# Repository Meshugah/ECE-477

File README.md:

# ECE 477 website backup

Senior design project website details.

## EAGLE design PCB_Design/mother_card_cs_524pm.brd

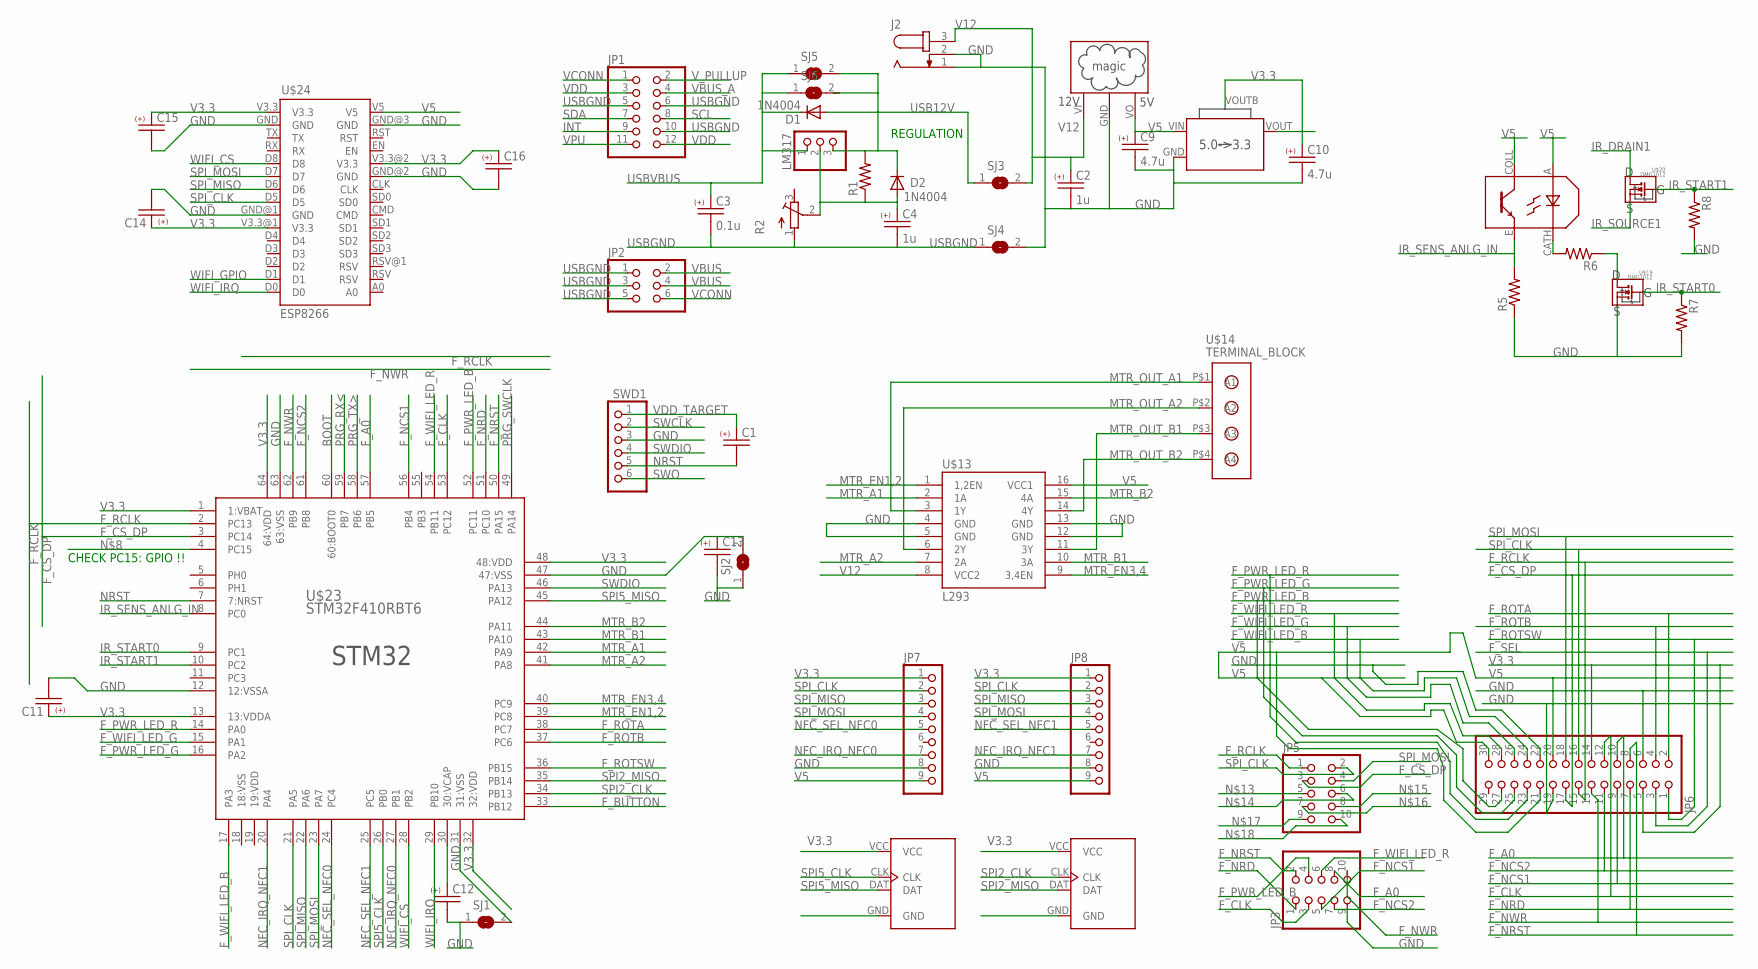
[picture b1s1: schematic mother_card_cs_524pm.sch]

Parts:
C1, C11, C12, C13, C14, C15, C16: C-USC0805; C0805
C2, C4: 1u; C0805
C3: 0.1u; C0805
C9, C10: 4.7u; C0805
D1, D2: 1N4004; DO41-10
J2: JACK-PLUG0; SPC4077
JP1: PINHD-2X6; 2X06
JP2: PINHD-2X3; 2X03
JP3, JP5: PINHD-2X5; 2X05
JP6: PINHD-2X15/SOCK; 2X15/SOCK
JP7, JP8: PINHD-1X9/90; 1X09/90
LM317: PINHD-1X3; 1X03
R1, R5, R6, R7, R8: R-US_R0805; R0805
R2: R-TRIMM64W; RTRIM64W
SJ1, SJ2, SJ3, SJ4, SJ5, SJ6: SJ
SWD1: PINHD-1X6; 1X06
U$13: L293; DIL16
U$14: TERMINAL_BLOCK; 1X4/BLOCK
U$15: AP2114H
U$16: OKI-78SR-W36; SIP3
U$18: TCRT5000
U$19, U$20: DMG1012; SOT323
U$21, U$22: HX711
U$23: STM32F410RBT6; QFP50P1200X1200X160-64N
U$24: ESP8266

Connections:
BOOT: U$23.60 (60:BOOT0)
F_A0: JP3.8, JP6.10, U$23.57 (PB5)
F_BUTTON: U$23.33 (PB12)
F_CLK: JP3.3, JP6.12, U$23.53 (PC12)
F_CS_DP: JP5.3, JP6.17, U$23.3 (PC14)
F_NCS1: JP3.5, JP6.9, U$23.56 (PB4)
F_NCS2: JP3.7, JP6.11, U$23.61 (PB8)
F_NRD: JP3.1, JP6.7, U$23.51 (PC10)
F_NRST: JP3.2, JP6.8, U$23.50 (PA15)
F_NWR: JP3.10, JP6.13, U$23.62 (PB9)
F_PWR_LED_B: JP3.4, JP6.27, U$23.52 (PC11)
F_PWR_LED_G: JP6.25, U$23.16 (PA2)
F_PWR_LED_R: JP6.23, U$23.14 (PA0)
F_RCLK: JP5.1, JP6.15, U$23.2 (PC13)
F_ROTA: JP6.2, U$23.38 (PC7)
F_ROTB: JP6.4, U$23.37 (PC6)
F_ROTSW: JP6.1, U$23.36 (PB15)
F_SEL: JP6.3
F_WIFI_LED_B: JP6.24, U$23.17 (PA3)
F_WIFI_LED_G: JP6.26, U$23.15 (PA1)
F_WIFI_LED_R: JP3.6, JP6.28, U$23.54 (PB11)
GND: C2.2, C9.2, C10.2, C11.2, C12.2, C13.1, C14.2, C15.2, C16.2, J2.1, J2.2, JP3.9, JP6.6, JP6.19, JP6.22, JP7.8, JP8.8, R5.1, R7.2, R8.2, SJ1.1, SJ1.2, SJ2.2, SJ4.2, SWD1.3, U$13.4 (GND), U$13.5 (GND), U$13.12 (GND), U$13.13 (GND), U$15.GND, U$16.GND, U$19.S, U$21.GND, U$22.GND, U$23.12 (12:VSSA), U$23.31 (31:VSS), U$23.47 (47:VSS), U$23.63 (63:VSS), U$24.GND, U$24.GND@1 (GND), U$24.GND@2 (GND), U$24.GND@3 (GND)
INT: JP1.9
IR_DRAIN1: U$20.D
IR_SENS_ANLG_IN: R5.2, U$18.E, U$23.8 (PC0)
IR_SOURCE1: U$20.S
IR_START0: R7.1, U$19.G, U$23.9 (PC1)
IR_START1: R8.1, U$20.G, U$23.10 (PC2)
MTR_A1: U$13.2 (1A), U$23.42 (PA9)
MTR_A2: U$13.7 (2A), U$23.41 (PA8)
MTR_B1: U$13.10 (3A), U$23.43 (PA10)
MTR_B2: U$13.15 (4A), U$23.44 (PA11)
MTR_EN1,2: U$13.1 (1,2EN), U$23.39 (PC8)
MTR_EN3,4: U$13.9 (3,4EN), U$23.40 (PC9)
MTR_OUT_A1: U$13.3 (1Y), U$14.P$1 (A1)
MTR_OUT_A2: U$13.6 (2Y), U$14.P$2 (A2)
MTR_OUT_B1: U$13.11 (3Y), U$14.P$3 (A3)
MTR_OUT_B2: U$13.14 (4Y), U$14.P$4 (A4)
unnamed: C12.1, U$23.30 (30:VCAP)
unnamed: C13.2, SJ2.1
unnamed: C4.1, D2.A, LM317.2, R1.1, R2.2 (S)
unnamed: R6.2, U$18.CATH
unnamed: R6.1, U$19.D
NFC_IRQ_NFC0: JP7.7, U$23.27 (PB1)
NFC_IRQ_NFC1: JP8.7, U$23.20 (PA4)
NFC_SEL_NFC0: JP7.5, U$23.24 (PC4)
NFC_SEL_NFC1: JP8.5, U$23.25 (PC5)
NRST: C1.2, SWD1.5, U$23.7 (7:NRST)
PRG_RX<: U$23.59 (PB7)
PRG_SWCLK: U$23.49 (PA14)
PRG_TX>: U$23.58 (PB6)
SCL: JP1.8
SDA: JP1.7
SPI2_CLK: U$22.CLK, U$23.34 (PB13)
SPI2_MISO: U$22.DAT, U$23.35 (PB14)
SPI5_CLK: U$21.CLK, U$23.26 (PB0)
SPI5_MISO: U$21.DAT, U$23.45 (PA12)
SPI_CLK: JP5.2, JP6.16, JP7.2, JP8.2, U$23.21 (PA5), U$24.D5
SPI_MISO: JP7.3, JP8.3, U$23.22 (PA6), U$24.D6
SPI_MOSI: JP5.4, JP6.18, JP7.4, JP8.4, U$23.23 (PA7), U$24.D7
SWCLK: SWD1.2
SWDIO: SWD1.4, U$23.46 (PA13)
SWO: SWD1.6
USB12V: D1.A, D2.C, LM317.3, R1.2, SJ3.1, SJ5.2
USBGND: C3.2, C4.2, JP1.5, JP1.6, JP1.10, JP2.1, JP2.3, JP2.5, R2.1 (A), SJ4.1
USBVBUS: C3.1, D1.C, LM317.1, SJ5.1, SJ6.1
V3.3: C10.1, C11.1, C14.1, C15.1, C16.1, JP6.5, JP6.14, JP7.1, JP8.1, U$15.VOUT (VO), U$15.VOUTB (BODY), U$21.VCC, U$22.VCC, U$23.1 (1:VBAT), U$23.13 (13:VDDA), U$23.32 (32:VDD), U$23.48 (48:VDD), U$23.64 (64:VDD), U$24.V3.3, U$24.V3.3@1 (V3.3), U$24.V3.3@2 (V3.3)
V5: C9.1, JP6.20, JP6.21, JP6.30, JP7.9, JP8.9, U$13.16 (VCC1), U$15.VIN (VI), U$16.VO, U$18.A, U$18.COLL, U$24.V5
V12: C2.1, J2.3, SJ3.2, U$13.8 (VCC2), U$16.VI
VBUS: JP2.2, JP2.4
VBUS_A: JP1.4
VCONN: JP1.1, JP2.6
VDD: JP1.3, JP1.12
VDD_TARGET: C1.1, SWD1.1
VPU: JP1.11
V_PULLUP: JP1.2
WIFI_CS: U$23.28 (PB2), U$24.D8
WIFI_GPIO: U$24.D1
WIFI_IRQ: U$23.29 (PB10), U$24.D0

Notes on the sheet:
REGULATION
CHECK PC15: GPIO !!

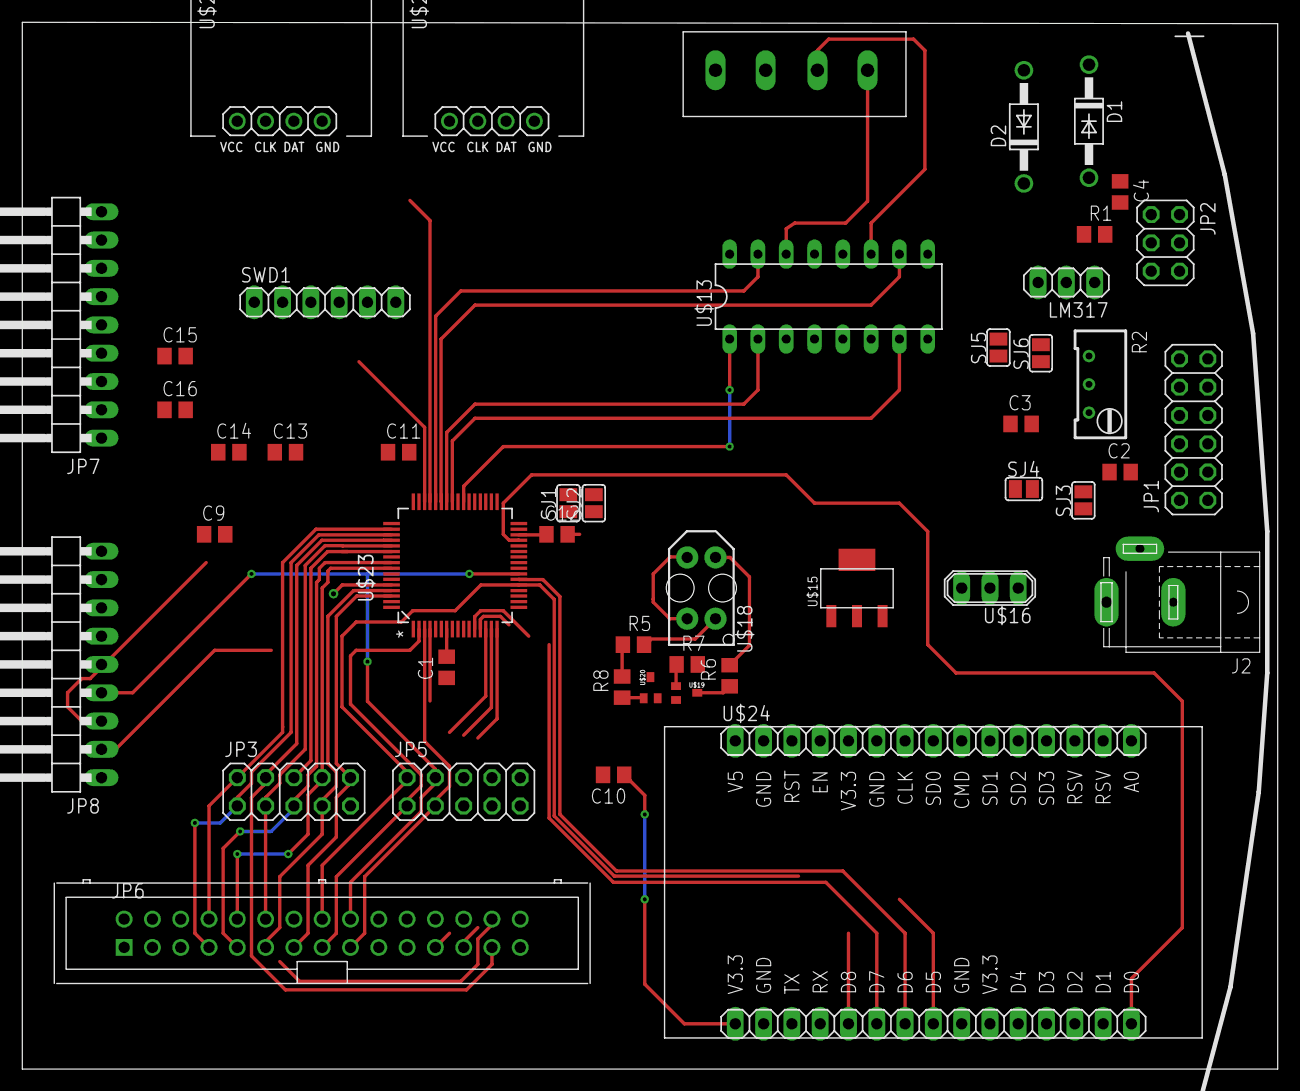
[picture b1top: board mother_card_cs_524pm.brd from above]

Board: 2 copper layers, 112.7 x 94.0 mm, 47 parts (0 on the bottom side), 62 nets.

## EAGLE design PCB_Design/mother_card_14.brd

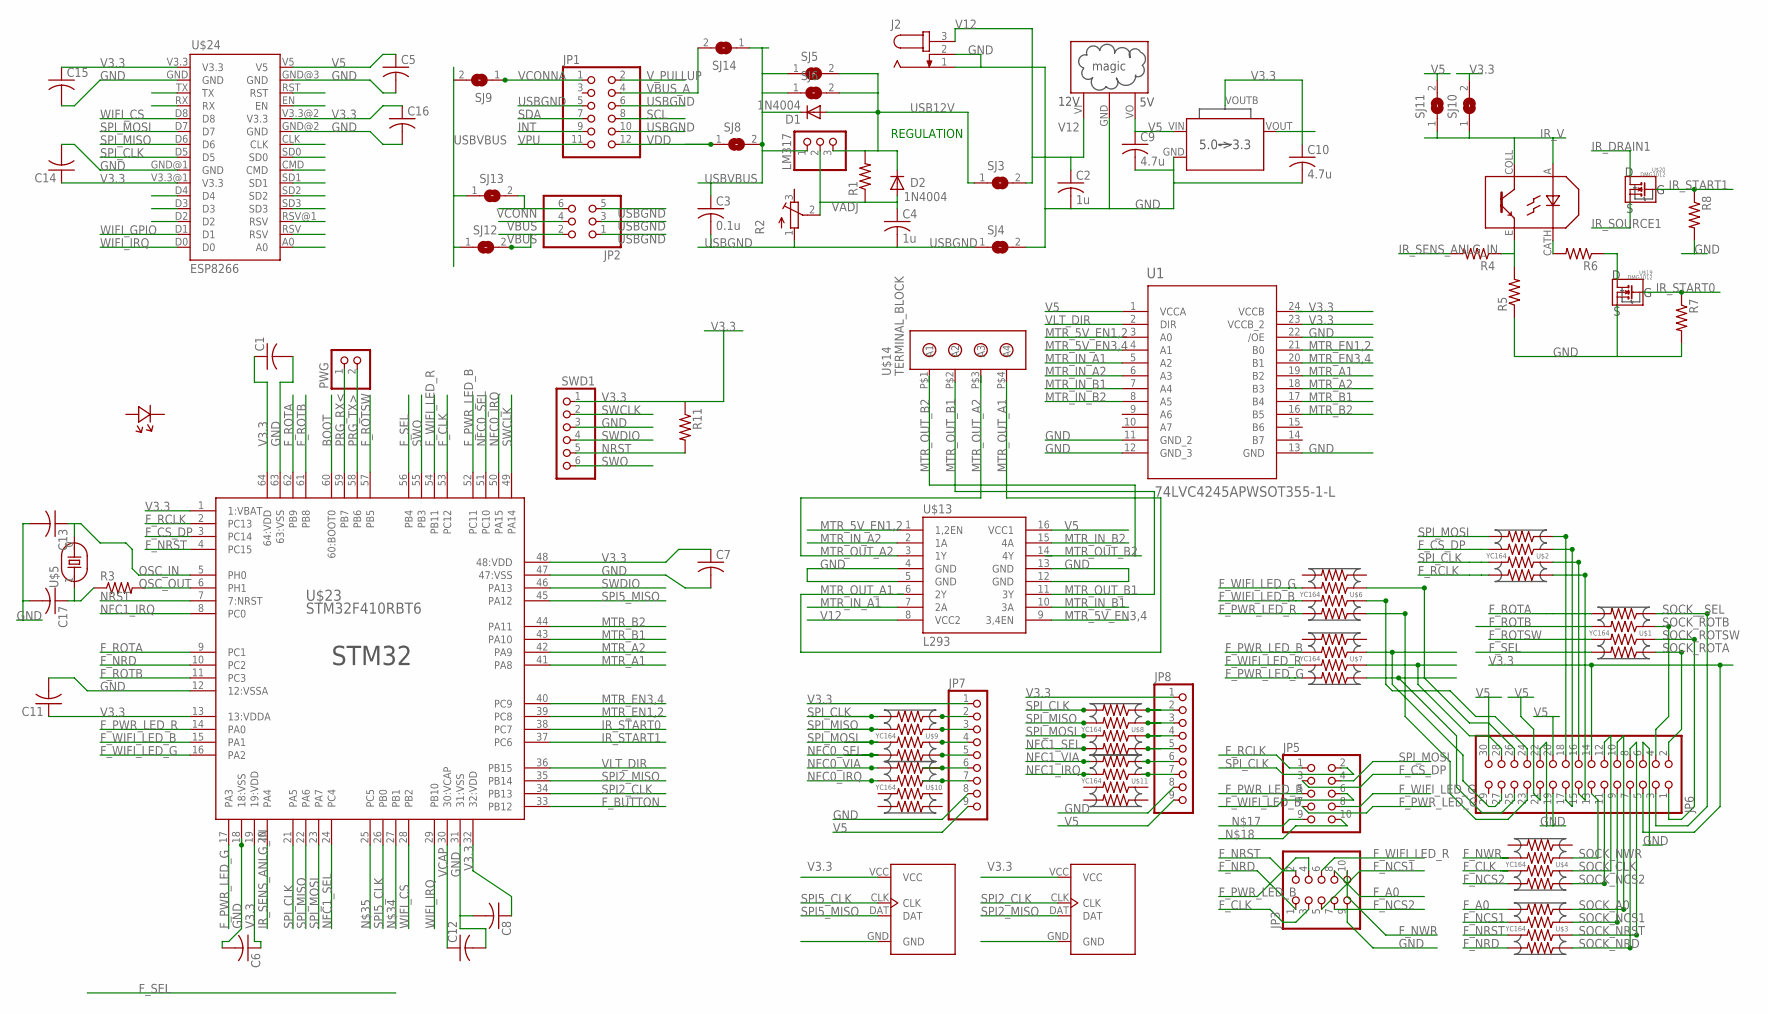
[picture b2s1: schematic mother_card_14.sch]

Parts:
C1, C5, C6, C7, C8, C11, C12, C14, C15, C16: C-USC0805; C0805
C2, C4: 1u; C0805
C3: 0.1u; C0805
C9, C10: 4.7u; C0805
C13, C17: C-USC0603; C0603
D1, D2: 1N4004; DO41-10
J2: JACK-PLUG0; SPC4077
JP1: PINHD-2X6; 2X06
JP2: PINHD-2X3; 2X03
JP3, JP5: PINHD-2X5; 2X05
JP6: PINHD-2X15/SOCK; 2X15/SOCK
JP7, JP8: PINHD-1X9/90; 1X09/90
LM317: PINHD-1X3; 1X03
PWG: PINHD-1X2; 1X02
R1, R3, R4, R5, R6, R7, R8, R11: R-US_R0805; R0805
R2: R-TRIMM64W; RTRIM64W
SJ3, SJ4, SJ5, SJ6, SJ8, SJ9, SJ10, SJ11, SJ12, SJ13, SJ14: SJ
SWD1: PINHD-1X6; 1X06
U1: 74LVC4245APWSOT355-1-L; SOT355-1-L
U$1, U$2, U$3, U$4, U$6, U$7, U$8, U$9, U$10, U$11: YC164
U$5: HC-49S_9B
U$12: LED0603; LED
U$13: L293; DIL16
U$14: TERMINAL_BLOCK; 1X4/BLOCK
U$15: AP2114H
U$16: OKI-78SR-W36; SIP3
U$18: TCRT5000
U$19, U$20: DMG1012; SOT323
U$21, U$22: HX711
U$23: STM32F410RBT6; QFP50P1200X1200X160-64N
U$24: ESP8266

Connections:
BOOT: U$23.60 (60:BOOT0)
F_A0: JP3.8, U$3.P$4 (4)
F_BUTTON: U$23.33 (PB12)
F_CLK: JP3.3, U$4.P$2 (2), U$23.53 (PC12)
F_CS_DP: JP5.3, U$2.P$3 (3), U$23.3 (PC14)
F_NCS1: JP3.5, U$3.P$3 (3)
F_NCS2: JP3.7, U$4.P$1 (1)
F_NRD: JP3.1, U$3.P$1 (1), U$23.10 (PC2)
F_NRST: JP3.2, U$3.P$2 (2), U$23.4 (PC15)
F_NWR: JP3.10, U$4.P$3 (3)
F_PWR_LED_B: JP3.4, U$7.P$3 (3), U$23.52 (PC11)
F_PWR_LED_G: JP5.7, U$7.P$1 (1), U$23.17 (PA3)
F_PWR_LED_R: JP5.5, U$6.P$1 (1), U$23.14 (PA0)
F_RCLK: JP5.1, U$2.P$1 (1), U$23.2 (PC13)
F_ROTA: U$1.P$4 (4), U$23.9 (PC1), U$23.62 (PB9)
F_ROTB: U$1.P$3 (3), U$23.11 (PC3), U$23.61 (PB8)
F_ROTSW: U$1.P$2 (2), U$23.57 (PB5)
F_SEL: U$1.P$1 (1), U$23.56 (PB4)
F_WIFI_LED_B: JP5.6, U$6.P$2 (2), U$23.15 (PA1)
F_WIFI_LED_G: JP5.8, U$6.P$3 (3), U$23.16 (PA2)
F_WIFI_LED_R: JP3.6, U$7.P$2 (2), U$23.54 (PB11)
GND: C1.2, C2.2, C5.2, C6.2, C7.2, C8.2, C9.2, C10.2, C11.2, C12.2, C13.2, C14.2, C15.2, C16.2, C17.2, J2.1, J2.2, JP3.9, JP6.6, JP6.19, JP6.22, JP7.8, JP8.8, R5.1, R7.2, R8.2, SJ4.2, SWD1.3, U1.11 (GND_2), U1.12 (GND_3), U1.13 (GND), U1.22 (/OE), U$13.4 (GND), U$13.5 (GND), U$13.12 (GND), U$13.13 (GND), U$15.GND, U$16.GND, U$19.S, U$21.GND, U$22.GND, U$23.12 (12:VSSA), U$23.18 (18:VSS), U$23.31 (31:VSS), U$23.47 (47:VSS), U$23.63 (63:VSS), U$24.GND, U$24.GND@1 (GND), U$24.GND@2 (GND), U$24.GND@3 (GND)
INT: JP1.9
IR_DRAIN1: U$20.D
IR_SENS_ANLG_IN: R4.2, U$23.20 (PA4)
IR_SOURCE1: U$20.S
IR_START0: R7.1, U$19.G, U$23.38 (PC7)
IR_START1: R8.1, U$20.G, U$23.37 (PC6)
IR_V: SJ10.1, SJ11.1, U$18.A, U$18.COLL
MTR_5V_EN1,2: U1.3 (A0), U$13.1 (1,2EN)
MTR_5V_EN3,4: U1.4 (A1), U$13.9 (3,4EN)
MTR_A1: U1.19 (B2), U$23.41 (PA8)
MTR_A2: U1.18 (B3), U$23.42 (PA9)
MTR_B1: U1.17 (B4), U$23.43 (PA10)
MTR_B2: U1.16 (B5), U$23.44 (PA11)
MTR_EN1,2: U1.21 (B0), U$23.39 (PC8)
MTR_EN3,4: U1.20 (B1), U$23.40 (PC9)
MTR_IN_A1: U1.5 (A2), U$13.7 (2A)
MTR_IN_A2: U1.6 (A3), U$13.2 (1A)
MTR_IN_B1: U1.7 (A4), U$13.10 (3A)
MTR_IN_B2: U1.8 (A5), U$13.15 (4A)
MTR_OUT_A1: U$13.6 (2Y), U$14.P$4 (A4)
MTR_OUT_A2: U$13.3 (1Y), U$14.P$3 (A3)
MTR_OUT_B1: U$13.11 (3Y), U$14.P$2 (A2)
MTR_OUT_B2: U$13.14 (4Y), U$14.P$1 (A1)
unnamed: JP7.6, U$10.P$44 (44)
unnamed: JP8.6, U$11.P$44 (44)
unnamed: R6.2, U$18.CATH
unnamed: R3.2, U$23.6 (PH1)
unnamed: R6.1, U$19.D
unnamed: JP8.2, U$8.P$44 (44)
unnamed: JP8.3, U$8.P$33 (33)
unnamed: JP8.4, U$8.P$22 (22)
unnamed: JP8.5, U$8.P$11 (11)
unnamed: JP8.7, U$11.P$33 (33)
unnamed: JP7.5, U$9.P$11 (11)
unnamed: JP7.4, U$9.P$22 (22)
unnamed: JP7.3, U$9.P$33 (33)
unnamed: JP7.2, U$9.P$44 (44)
unnamed: JP7.7, U$10.P$33 (33)
unnamed: R4.1, R5.2, U$18.E
NFC0_IRQ: U$10.P$3 (3), U$23.50 (PA15)
NFC0_SEL: U$9.P$1 (1), U$23.51 (PC10)
NFC0_VIA: U$10.P$4 (4)
NFC1_IRQ: U$11.P$3 (3), U$23.8 (PC0)
NFC1_SEL: U$8.P$1 (1), U$23.24 (PC4)
NFC1_VIA: U$11.P$4 (4)
NRST: R11.2, SWD1.5, U$23.7 (7:NRST)
OSC_IN: C13.1, U$5.0, U$23.5 (PH0)
OSC_OUT: C17.1, R3.1, U$5.1
PRG_RX<: PWG.1, U$23.59 (PB7)
PRG_TX>: PWG.2, U$23.58 (PB6)
SCL: JP1.8
SDA: JP1.7
SOCK_A0: JP6.10, U$3.P$44 (44)
SOCK_CLK: JP6.12, U$4.P$22 (22)
SOCK_NCS1: JP6.9, U$3.P$33 (33)
SOCK_NCS2: JP6.11, U$4.P$11 (11)
SOCK_NRD: JP6.7, U$3.P$11 (11)
SOCK_NRST: JP6.8, U$3.P$22 (22)
SOCK_NWR: JP6.13, U$4.P$33 (33)
SOCK_PWR_LED_B: JP6.27, U$7.P$33 (33)
SOCK_PWR_LED_G: JP6.25, U$7.P$11 (11)
SOCK_PWR_LED_R: JP6.23, U$6.P$11 (11)
SOCK_ROTA: JP6.2, U$1.P$11 (11)
SOCK_ROTB: JP6.4, U$1.P$33 (33)
SOCK_ROTSW: JP6.1, U$1.P$22 (22)
SOCK_SPI_CLK: JP6.16, U$2.P$22 (22)
SOCK_SPI_MOSI: JP6.18, U$2.P$44 (44)
SOCK_WIFI_LED_B: JP6.24, U$6.P$22 (22)
SOCK_WIFI_LED_G: JP6.26, U$6.P$33 (33)
SOCK_WIFI_LED_R: JP6.28, U$7.P$22 (22)
SOCK__CS_DP: JP6.17, U$2.P$33 (33)
SOCK__RCLK: JP6.15, U$2.P$11 (11)
SOCK__SEL: JP6.3, U$1.P$44 (44)
SPI2_CLK: U$22.CLK, U$23.34 (PB13)
SPI2_MISO: U$22.DAT, U$23.35 (PB14)
SPI5_CLK: U$21.CLK, U$23.26 (PB0)
SPI5_MISO: U$21.DAT, U$23.45 (PA12)
SPI_CLK: JP5.2, U$2.P$2 (2), U$8.P$4 (4), U$9.P$4 (4), U$23.21 (PA5), U$24.D5
SPI_MISO: U$8.P$3 (3), U$9.P$3 (3), U$23.22 (PA6), U$24.D6
SPI_MOSI: JP5.4, U$2.P$4 (4), U$8.P$2 (2), U$9.P$2 (2), U$23.23 (PA7), U$24.D7
SWCLK: SWD1.2, U$23.49 (PA14)
SWDIO: SWD1.4, U$23.46 (PA13)
SWO: SWD1.6, U$23.55 (PB3)
USB12V: D1.A, D2.C, LM317.3, R1.2, SJ3.1, SJ5.2, SJ6.2
USBGND: C3.2, C4.2, JP1.5, JP1.6, JP1.10, JP2.1, JP2.3, JP2.5, R2.1 (A), SJ4.1
USBVBUS: C3.1, D1.C, LM317.1, SJ5.1, SJ6.1, SJ8.2, SJ9.2, SJ12.1, SJ13.1, SJ14.1
V3.3: C1.1, C6.1, C7.1, C8.1, C10.1, C11.1, C14.1, C15.1, C16.1, JP6.5, JP6.14, JP7.1, JP8.1, R11.1, SJ10.2, SWD1.1, U1.23 (VCCB_2), U1.24 (VCCB), U$15.VOUT (VO), U$15.VOUTB (BODY), U$21.VCC, U$22.VCC, U$23.1 (1:VBAT), U$23.13 (13:VDDA), U$23.19 (19:VDD), U$23.32 (32:VDD), U$23.48 (48:VDD), U$23.64 (64:VDD), U$24.V3.3, U$24.V3.3@1 (V3.3), U$24.V3.3@2 (V3.3)
V5: C5.1, C9.1, JP6.20, JP6.21, JP6.30, JP7.9, JP8.9, SJ11.2, U1.1 (VCCA), U$13.16 (VCC1), U$15.VIN (VI), U$16.VO, U$24.V5
V12: C2.1, J2.3, SJ3.2, U$13.8 (VCC2), U$16.VI
VADJ: C4.1, D2.A, LM317.2, R1.1, R2.2 (S)
VBUS: JP2.2, JP2.4, SJ12.2
VBUS_A: JP1.4, SJ14.2
VCAP: C12.1, U$23.30 (30:VCAP)
VCONN: JP2.6, SJ13.2
VCONNA: JP1.1, SJ9.1
VDD: JP1.12, SJ8.1
VLT_DIR: U1.2 (DIR), U$23.36 (PB15)
VPU: JP1.11
V_PULLUP: JP1.2
WIFI_CS: U$23.28 (PB2), U$24.D8
WIFI_GPIO: U$24.D1
WIFI_IRQ: U$23.29 (PB10), U$24.D0

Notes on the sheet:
REGULATION

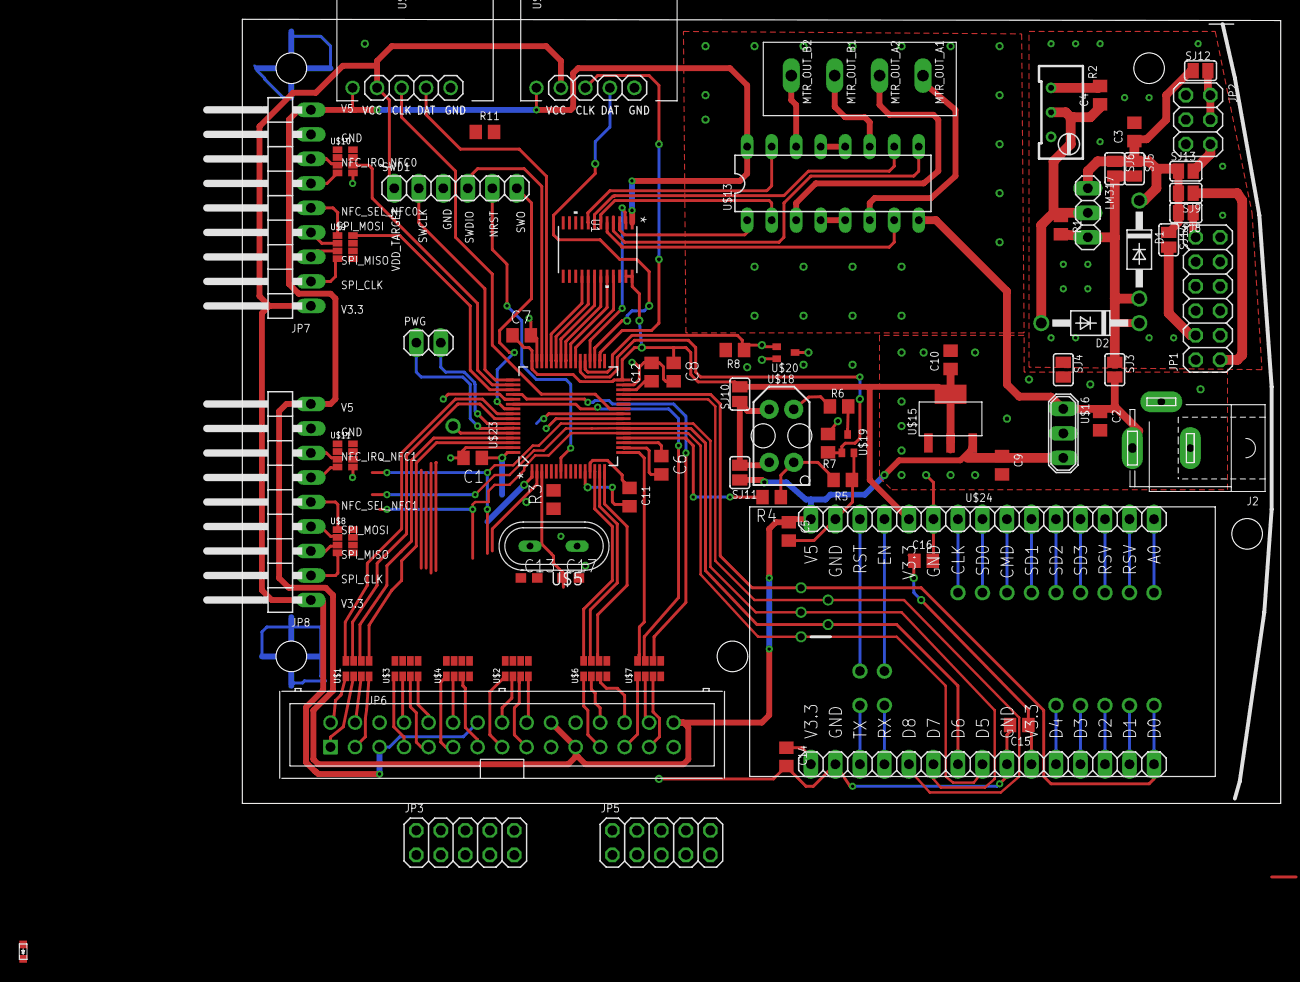
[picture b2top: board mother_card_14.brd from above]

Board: 2 copper layers, 107.6 x 81.3 mm, 74 parts (0 on the bottom side), 112 nets.

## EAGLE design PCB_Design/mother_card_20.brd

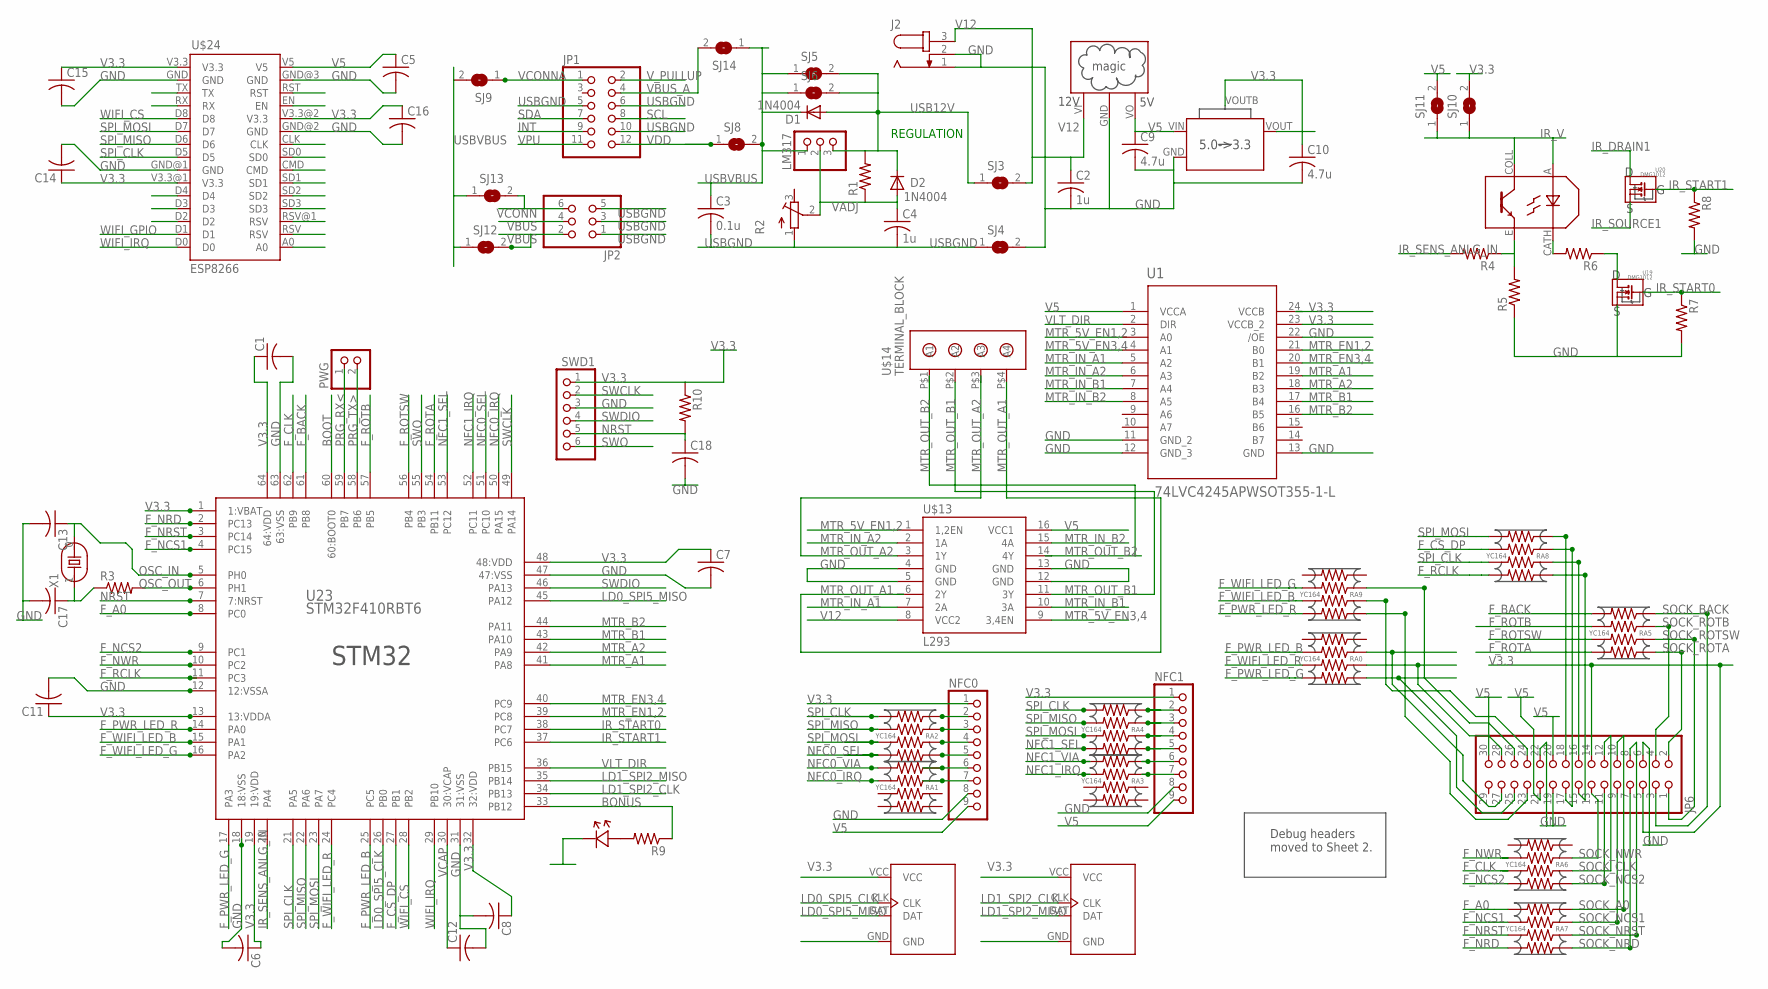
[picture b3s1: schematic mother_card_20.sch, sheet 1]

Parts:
C1, C5, C6, C7, C8, C11, C12, C14, C15, C16, C18: C-USC0805; C0805
C2, C4: 1u; C0805
C3: 0.1u; C0805
C9, C10: 4.7u; C0805
C13, C17: C-USC0603; C0603
D1, D2: 1N4004; DO41-10
IRSENS: TCRT5000
J2: JACK-PLUG0; SPC4077
JP1: PINHD-2X6; 2X06
JP2: PINHD-2X3; 2X03
JP6: PINHD-2X15/SOCK; 2X15/SOCK
LM317: PINHD-1X3; 1X03
NFC0, NFC1: PINHD-1X9; 1X09
PWG: PINHD-1X2; 1X02
R1, R3, R4, R5, R6, R7, R8, R9, R10: R-US_R0805; R0805
R2: R-TRIMM64W; RTRIM64W
RA0, RA1, RA2, RA3, RA4, RA5, RA6, RA7, RA8, RA9: YC164
SJ3, SJ4, SJ5, SJ6, SJ8, SJ9, SJ10, SJ11, SJ12, SJ13, SJ14: SJ
SWD1: PINHD-1X6; 1X06
U1: 74LVC4245APWSOT355-1-L; SOT355-1-L
U19, U20: DMG1012; SOT323
U23: STM32F410RBT6; QFP50P1200X1200X160-64N
U$1: LED0603; LED
U$13: L293; DIL16
U$14: TERMINAL_BLOCK; 1X4/BLOCK
U$15: AP2114H
U$16: OKI-78SR-W36; SIP3
U$21, U$22: HX711
U$24: ESP8266
X1: HC-49S_9B

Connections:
BONUS: R9.1, U23.33 (PB12)
BOOT: U23.60 (60:BOOT0)
F_A0: RA7.P$4 (4), U23.8 (PC0); also elsewhere on the board
F_BACK: RA5.P$4 (4), U23.61 (PB8); also elsewhere on the board
F_CLK: RA6.P$2 (2), U23.62 (PB9); also elsewhere on the board
F_CS_DP: RA8.P$3 (3), U23.27 (PB1); also elsewhere on the board
F_NCS1: RA7.P$3 (3), U23.4 (PC15); also elsewhere on the board
F_NCS2: RA6.P$1 (1), U23.9 (PC1); also elsewhere on the board
F_NRD: RA7.P$1 (1), U23.2 (PC13); also elsewhere on the board
F_NRST: RA7.P$2 (2), U23.3 (PC14); also elsewhere on the board
F_NWR: RA6.P$3 (3), U23.10 (PC2); also elsewhere on the board
F_PWR_LED_B: RA0.P$3 (3), U23.25 (PC5); also elsewhere on the board
F_PWR_LED_G: RA0.P$1 (1), U23.17 (PA3); also elsewhere on the board
F_PWR_LED_R: RA9.P$1 (1), U23.14 (PA0); also elsewhere on the board
F_RCLK: RA8.P$1 (1), U23.11 (PC3); also elsewhere on the board
F_ROTA: RA5.P$1 (1), U23.54 (PB11); also elsewhere on the board
F_ROTB: RA5.P$3 (3), U23.57 (PB5); also elsewhere on the board
F_ROTSW: RA5.P$2 (2), U23.56 (PB4); also elsewhere on the board
F_WIFI_LED_B: RA9.P$2 (2), U23.15 (PA1); also elsewhere on the board
F_WIFI_LED_G: RA9.P$3 (3), U23.16 (PA2); also elsewhere on the board
F_WIFI_LED_R: RA0.P$2 (2), U23.24 (PC4); also elsewhere on the board
GND: C1.2, C2.2, C5.2, C6.2, C7.2, C8.2, C9.2, C10.2, C11.2, C12.2, C13.2, C14.2, C15.2, C16.2, C17.2, C18.2, J2.1, J2.2, JP6.6, JP6.19, JP6.22, NFC0.8, NFC1.8, R5.1, R7.2, R8.2, SJ4.2, SWD1.3, U1.11 (GND_2), U1.12 (GND_3), U1.13 (GND), U1.22 (/OE), U19.S, U23.12 (12:VSSA), U23.18 (18:VSS), U23.31 (31:VSS), U23.47 (47:VSS), U23.63 (63:VSS), U$13.4 (GND), U$13.5 (GND), U$13.12 (GND), U$13.13 (GND), U$15.GND, U$16.GND, U$21.GND, U$22.GND, U$24.GND, U$24.GND@1 (GND), U$24.GND@2 (GND), U$24.GND@3 (GND); also elsewhere on the board
INT: JP1.9
IR_DRAIN1: U20.D
IR_SENS_ANLG_IN: R4.2, U23.20 (PA4)
IR_SOURCE1: U20.S
IR_START0: R7.1, U19.G, U23.38 (PC7)
IR_START1: R8.1, U20.G, U23.37 (PC6)
IR_V: IRSENS.A, IRSENS.COLL, SJ10.1, SJ11.1
LD0_SPI5_CLK: U23.26 (PB0), U$21.CLK
LD0_SPI5_MISO: U23.45 (PA12), U$21.DAT
LD1_SPI2_CLK: U23.34 (PB13), U$22.CLK
LD1_SPI2_MISO: U23.35 (PB14), U$22.DAT
MTR_5V_EN1,2: U1.3 (A0), U$13.1 (1,2EN)
MTR_5V_EN3,4: U1.4 (A1), U$13.9 (3,4EN)
MTR_A1: U1.19 (B2), U23.41 (PA8)
MTR_A2: U1.18 (B3), U23.42 (PA9)
MTR_B1: U1.17 (B4), U23.43 (PA10)
MTR_B2: U1.16 (B5), U23.44 (PA11)
MTR_EN1,2: U1.21 (B0), U23.39 (PC8)
MTR_EN3,4: U1.20 (B1), U23.40 (PC9)
MTR_IN_A1: U1.5 (A2), U$13.7 (2A)
MTR_IN_A2: U1.6 (A3), U$13.2 (1A)
MTR_IN_B1: U1.7 (A4), U$13.10 (3A)
MTR_IN_B2: U1.8 (A5), U$13.15 (4A)
MTR_OUT_A1: U$13.6 (2Y), U$14.P$4 (A4)
MTR_OUT_A2: U$13.3 (1Y), U$14.P$3 (A3)
MTR_OUT_B1: U$13.11 (3Y), U$14.P$2 (A2)
MTR_OUT_B2: U$13.14 (4Y), U$14.P$1 (A1)
unnamed: NFC0.6, RA1.P$44 (44)
unnamed: NFC1.6, RA3.P$44 (44)
unnamed: IRSENS.CATH, R6.2
unnamed: R3.2, U23.6 (PH1)
unnamed: R6.1, U19.D
unnamed: R9.2, U$1.ANODE (AN)
unnamed: NFC1.2, RA4.P$44 (44)
unnamed: NFC1.3, RA4.P$33 (33)
unnamed: NFC1.4, RA4.P$22 (22)
unnamed: NFC1.5, RA4.P$11 (11)
unnamed: NFC1.7, RA3.P$33 (33)
unnamed: NFC0.5, RA2.P$11 (11)
unnamed: NFC0.4, RA2.P$22 (22)
unnamed: NFC0.3, RA2.P$33 (33)
unnamed: NFC0.2, RA2.P$44 (44)
unnamed: NFC0.7, RA1.P$33 (33)
unnamed: IRSENS.E, R4.1, R5.2
NFC0_IRQ: RA1.P$3 (3), U23.50 (PA15)
NFC0_SEL: RA2.P$1 (1), U23.51 (PC10)
NFC0_VIA: RA1.P$4 (4)
NFC1_IRQ: RA3.P$3 (3), U23.52 (PC11)
NFC1_SEL: RA4.P$1 (1), U23.53 (PC12)
NFC1_VIA: RA3.P$4 (4)
NRST: C18.1, R10.2, SWD1.5, U23.7 (7:NRST); also elsewhere on the board
OSC_IN: C13.1, U23.5 (PH0), X1.0
OSC_OUT: C17.1, R3.1, X1.1
PRG_RX<: PWG.1, U23.59 (PB7)
PRG_TX>: PWG.2, U23.58 (PB6)
SCL: JP1.8
SDA: JP1.7
SOCK_A0: JP6.10, RA7.P$44 (44)
SOCK_BACK: JP6.3, RA5.P$44 (44)
SOCK_CLK: JP6.12, RA6.P$22 (22)
SOCK_NCS1: JP6.9, RA7.P$33 (33)
SOCK_NCS2: JP6.11, RA6.P$11 (11)
SOCK_NRD: JP6.7, RA7.P$11 (11)
SOCK_NRST: JP6.8, RA7.P$22 (22)
SOCK_NWR: JP6.13, RA6.P$33 (33)
SOCK_PWR_LED_B: JP6.27, RA0.P$33 (33)
SOCK_PWR_LED_G: JP6.25, RA0.P$11 (11)
SOCK_PWR_LED_R: JP6.23, RA9.P$11 (11)
SOCK_ROTA: JP6.2, RA5.P$11 (11)
SOCK_ROTB: JP6.4, RA5.P$33 (33)
SOCK_ROTSW: JP6.1, RA5.P$22 (22)
SOCK_SPI_CLK: JP6.16, RA8.P$22 (22)
SOCK_SPI_MOSI: JP6.18, RA8.P$44 (44)
SOCK_WIFI_LED_B: JP6.24, RA9.P$22 (22)
SOCK_WIFI_LED_G: JP6.26, RA9.P$33 (33)
SOCK_WIFI_LED_R: JP6.28, RA0.P$22 (22)
SOCK__CS_DP: JP6.17, RA8.P$33 (33)
SOCK__RCLK: JP6.15, RA8.P$11 (11)
SPI_CLK: RA2.P$4 (4), RA4.P$4 (4), RA8.P$2 (2), U23.21 (PA5), U$24.D5; also elsewhere on the board
SPI_MISO: RA2.P$3 (3), RA4.P$3 (3), U23.22 (PA6), U$24.D6
SPI_MOSI: RA2.P$2 (2), RA4.P$2 (2), RA8.P$4 (4), U23.23 (PA7), U$24.D7; also elsewhere on the board
SWCLK: SWD1.2, U23.49 (PA14)
SWDIO: SWD1.4, U23.46 (PA13)
SWO: SWD1.6, U23.55 (PB3)
USB12V: D1.A, D2.C, LM317.3, R1.2, SJ3.1, SJ5.2, SJ6.2
USBGND: C3.2, C4.2, JP1.5, JP1.6, JP1.10, JP2.1, JP2.3, JP2.5, R2.1 (A), SJ4.1; also elsewhere on the board
USBVBUS: C3.1, D1.C, LM317.1, SJ5.1, SJ6.1, SJ8.2, SJ9.2, SJ12.1, SJ13.1, SJ14.1
V3.3: C1.1, C6.1, C7.1, C8.1, C10.1, C11.1, C14.1, C15.1, C16.1, JP6.5, JP6.14, NFC0.1, NFC1.1, R10.1, SJ10.2, SWD1.1, U1.23 (VCCB_2), U1.24 (VCCB), U23.1 (1:VBAT), U23.13 (13:VDDA), U23.19 (19:VDD), U23.32 (32:VDD), U23.48 (48:VDD), U23.64 (64:VDD), U$15.VOUT (VO), U$15.VOUTB (BODY), U$21.VCC, U$22.VCC, U$24.V3.3, U$24.V3.3@1 (V3.3), U$24.V3.3@2 (V3.3); also elsewhere on the board
V5: C5.1, C9.1, JP6.20, JP6.21, JP6.30, NFC0.9, NFC1.9, SJ11.2, U1.1 (VCCA), U$13.16 (VCC1), U$15.VIN (VI), U$16.VO, U$24.V5; also elsewhere on the board
V12: C2.1, J2.3, SJ3.2, U$13.8 (VCC2), U$16.VI
VADJ: C4.1, D2.A, LM317.2, R1.1, R2.2 (S)
VBUS: JP2.2, JP2.4, SJ12.2
VBUS_A: JP1.4, SJ14.2
VCAP: C12.1, U23.30 (30:VCAP)
VCONN: JP2.6, SJ13.2
VCONNA: JP1.1, SJ9.1
VDD: JP1.12, SJ8.1
VLT_DIR: U1.2 (DIR), U23.36 (PB15)
VPU: JP1.11
V_PULLUP: JP1.2
WIFI_CS: U23.28 (PB2), U$24.D8
WIFI_GPIO: U$24.D1
WIFI_IRQ: U23.29 (PB10), U$24.D0

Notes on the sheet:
REGULATION
Debug headers moved to Sheet 2.

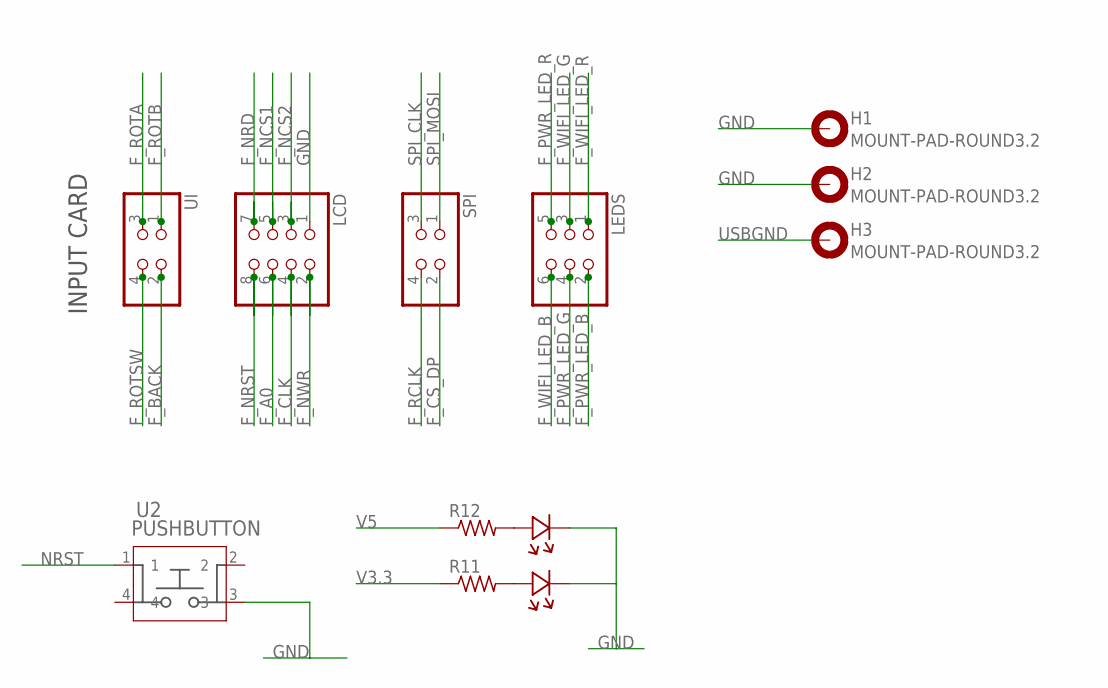
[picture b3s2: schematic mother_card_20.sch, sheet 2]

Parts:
H1, H2, H3: MOUNT-PAD-ROUND3.2; 3,2-PAD
LCD: PINHD-2X4; 2X04
LEDS: PINHD-2X3; 2X03
R11, R12: R-US_R0805; R0805
SPI: PINHD-2X2; 2X02
U2: PUSHBUTTON; SWITCH_FSM14JH
U$2, U$3: LED0603; LED
UI: PINHD-2X2; 2X02

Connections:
F_A0: LCD.6; also elsewhere on the board
F_BACK: UI.2; also elsewhere on the board
F_CLK: LCD.4; also elsewhere on the board
F_CS_DP: SPI.2; also elsewhere on the board
F_NCS1: LCD.5; also elsewhere on the board
F_NCS2: LCD.3; also elsewhere on the board
F_NRD: LCD.7; also elsewhere on the board
F_NRST: LCD.8; also elsewhere on the board
F_NWR: LCD.2; also elsewhere on the board
F_PWR_LED_B: LEDS.2; also elsewhere on the board
F_PWR_LED_G: LEDS.4; also elsewhere on the board
F_PWR_LED_R: LEDS.5; also elsewhere on the board
F_RCLK: SPI.4; also elsewhere on the board
F_ROTA: UI.3; also elsewhere on the board
F_ROTB: UI.1; also elsewhere on the board
F_ROTSW: UI.4; also elsewhere on the board
F_WIFI_LED_B: LEDS.6; also elsewhere on the board
F_WIFI_LED_G: LEDS.3; also elsewhere on the board
F_WIFI_LED_R: LEDS.1; also elsewhere on the board
GND: H1.B3,2, H2.B3,2, LCD.1, U2.3, U$2.CATHODE (CA), U$3.CATHODE (CA); also elsewhere on the board
unnamed: R12.2, U$3.ANODE (AN)
unnamed: R11.2, U$2.ANODE (AN)
NRST: U2.1; also elsewhere on the board
SPI_CLK: SPI.3; also elsewhere on the board
SPI_MOSI: SPI.1; also elsewhere on the board
USBGND: H3.B3,2; also elsewhere on the board
V3.3: R11.1; also elsewhere on the board
V5: R12.1; also elsewhere on the board

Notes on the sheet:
INPUT CARD

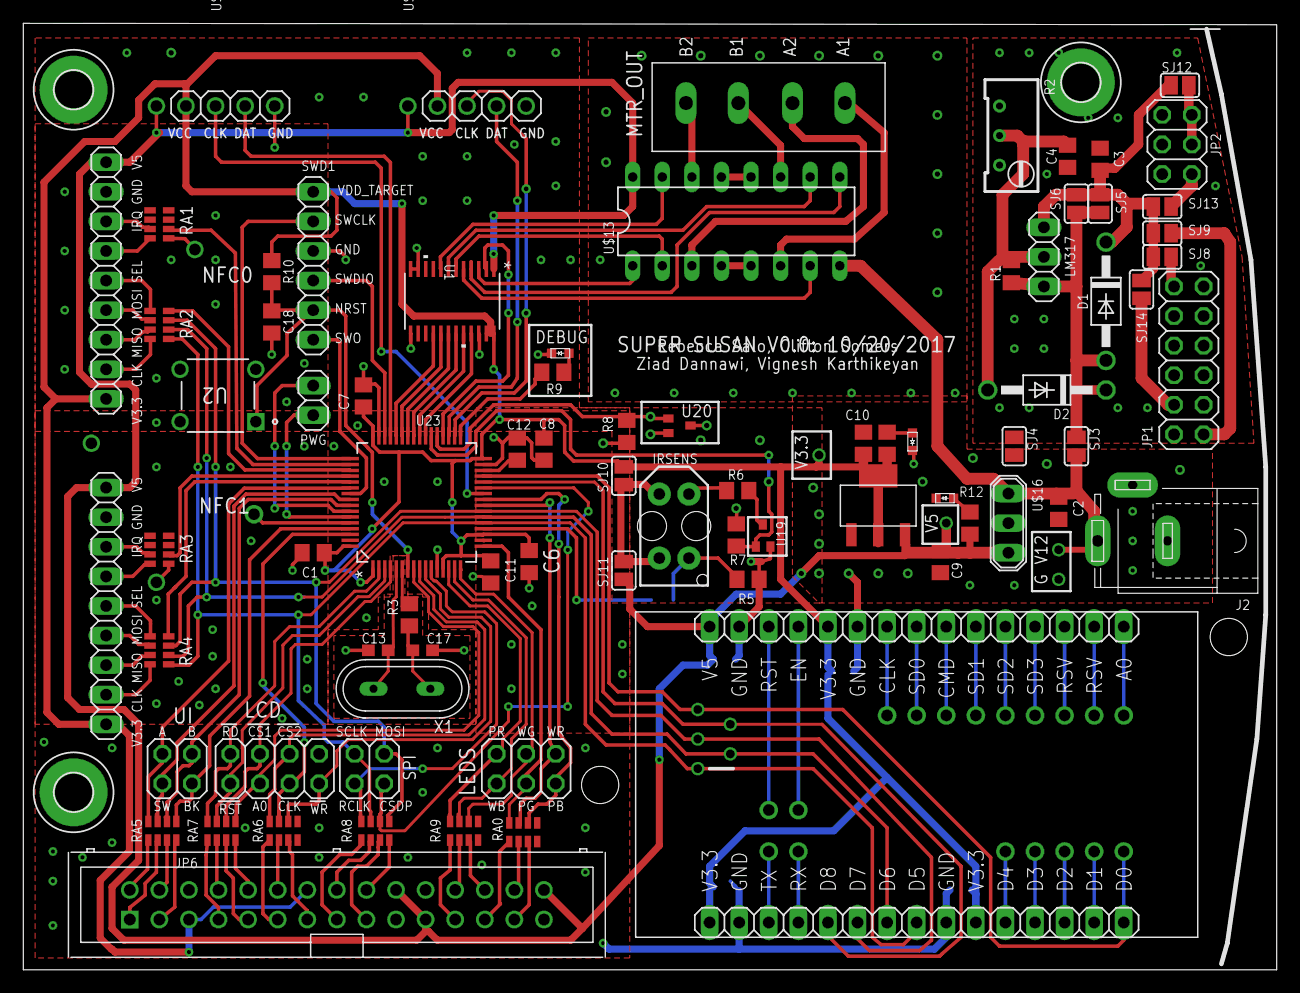
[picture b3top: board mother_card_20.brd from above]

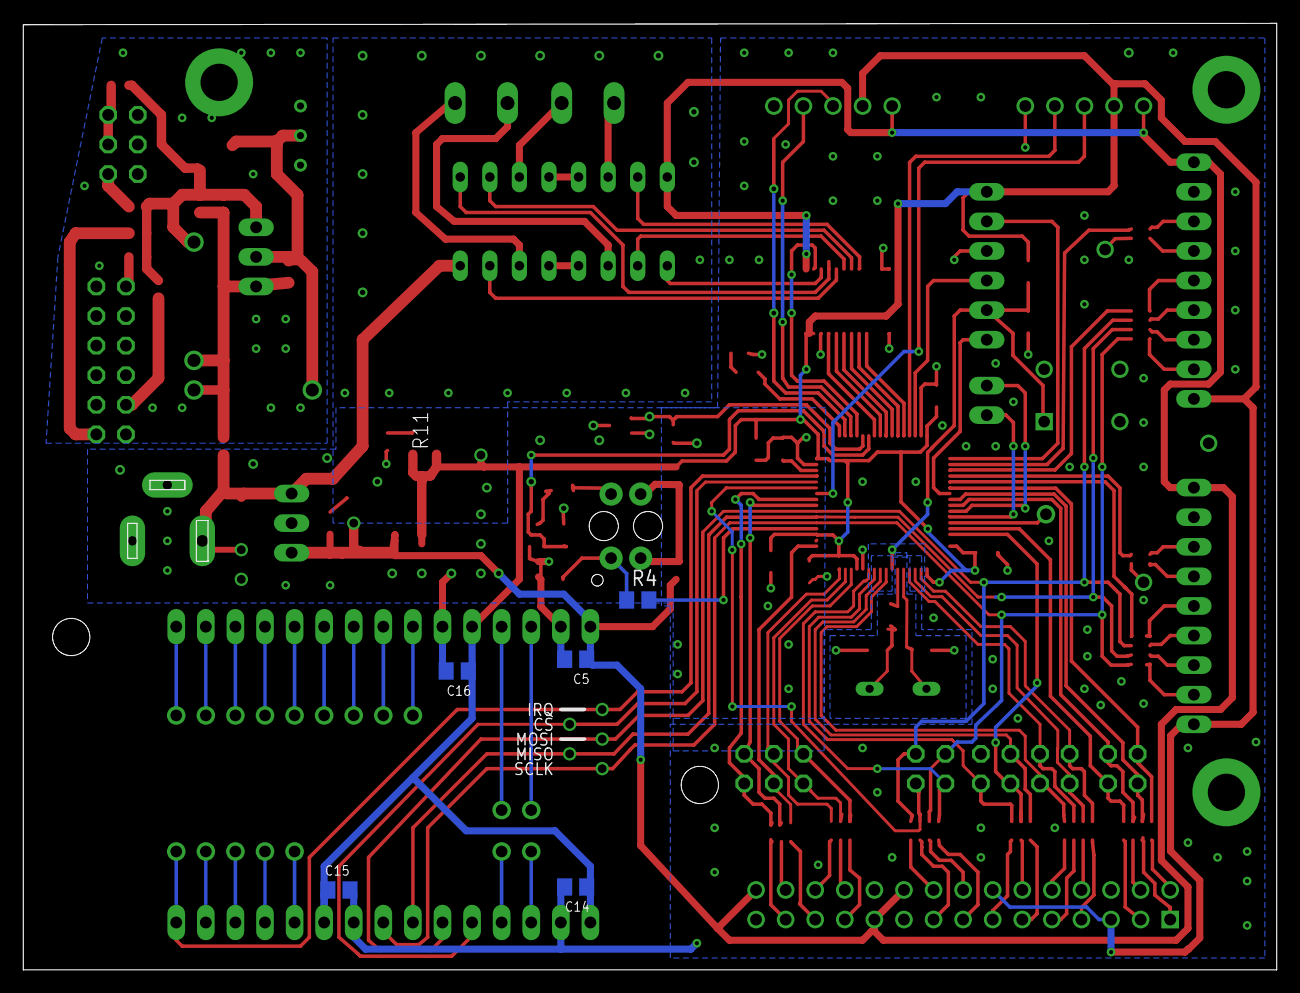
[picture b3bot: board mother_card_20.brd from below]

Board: 2 copper layers, 107.6 x 81.3 mm, 86 parts (5 on the bottom side), 116 nets.

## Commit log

2017-08-24 week 1 project website
2017-09-16 as of week 4, all folder structure cleaned up, seperate directories. Attempting to merge all into one super-repo
2017-10-28 week 10 website commit
